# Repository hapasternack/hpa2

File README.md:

Copyright (c) 2020-2025 Henry A. Pasternack.  All rights reserved.

28-Jan-2026:
The project is up-to-date with KiCad 9.06. There are no ERC or DRC errors.

The project-local footprint library, HPA2-footprints.pretty, contains the following footprints.

   Custom footprints:
   1-pad-wire-connector-22-ga
   2-pad-wire-connector-22-ga
   2-pad-wire-connector-small
   3-pad-wire-connector-22-ga
   HPA-Output-Coil
   Semitec-CRD-SMD

   Legacy footprints to avoid breaking changes to the layout:
   TO-71-6
   D_DO-34_SOD68_P7.62mm_Horizontal
   D_DO-35_SOD27_P7.62mm_Horizontal
   R_0805_2012Metric_Pad1.15x1.40mm_HandSolder
   TO-126-3_Vertical
   TSOT-23-5

   All other footprints have been updated from the latest release libraries as of KiCad 9.0.6.

The project-local library, HPA2_symbols, contains the following custom schematic symbols.

   2N5564
   CRD
   ADA4627-1

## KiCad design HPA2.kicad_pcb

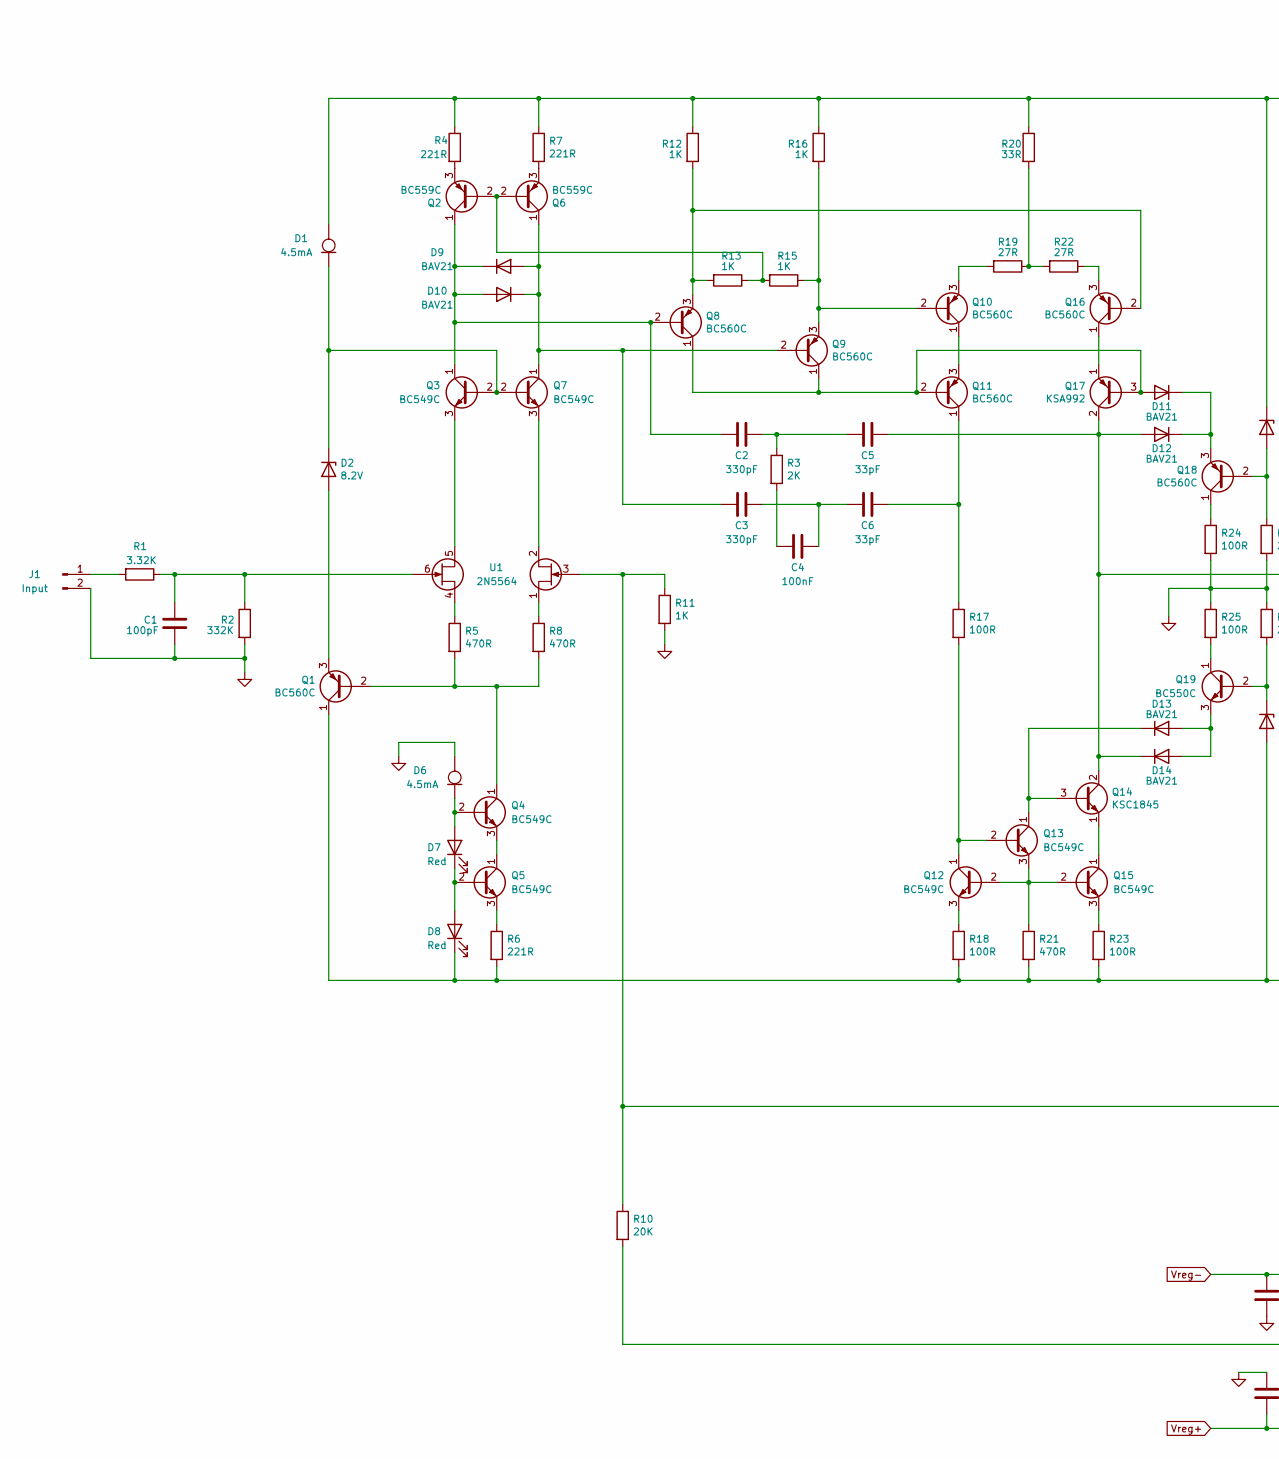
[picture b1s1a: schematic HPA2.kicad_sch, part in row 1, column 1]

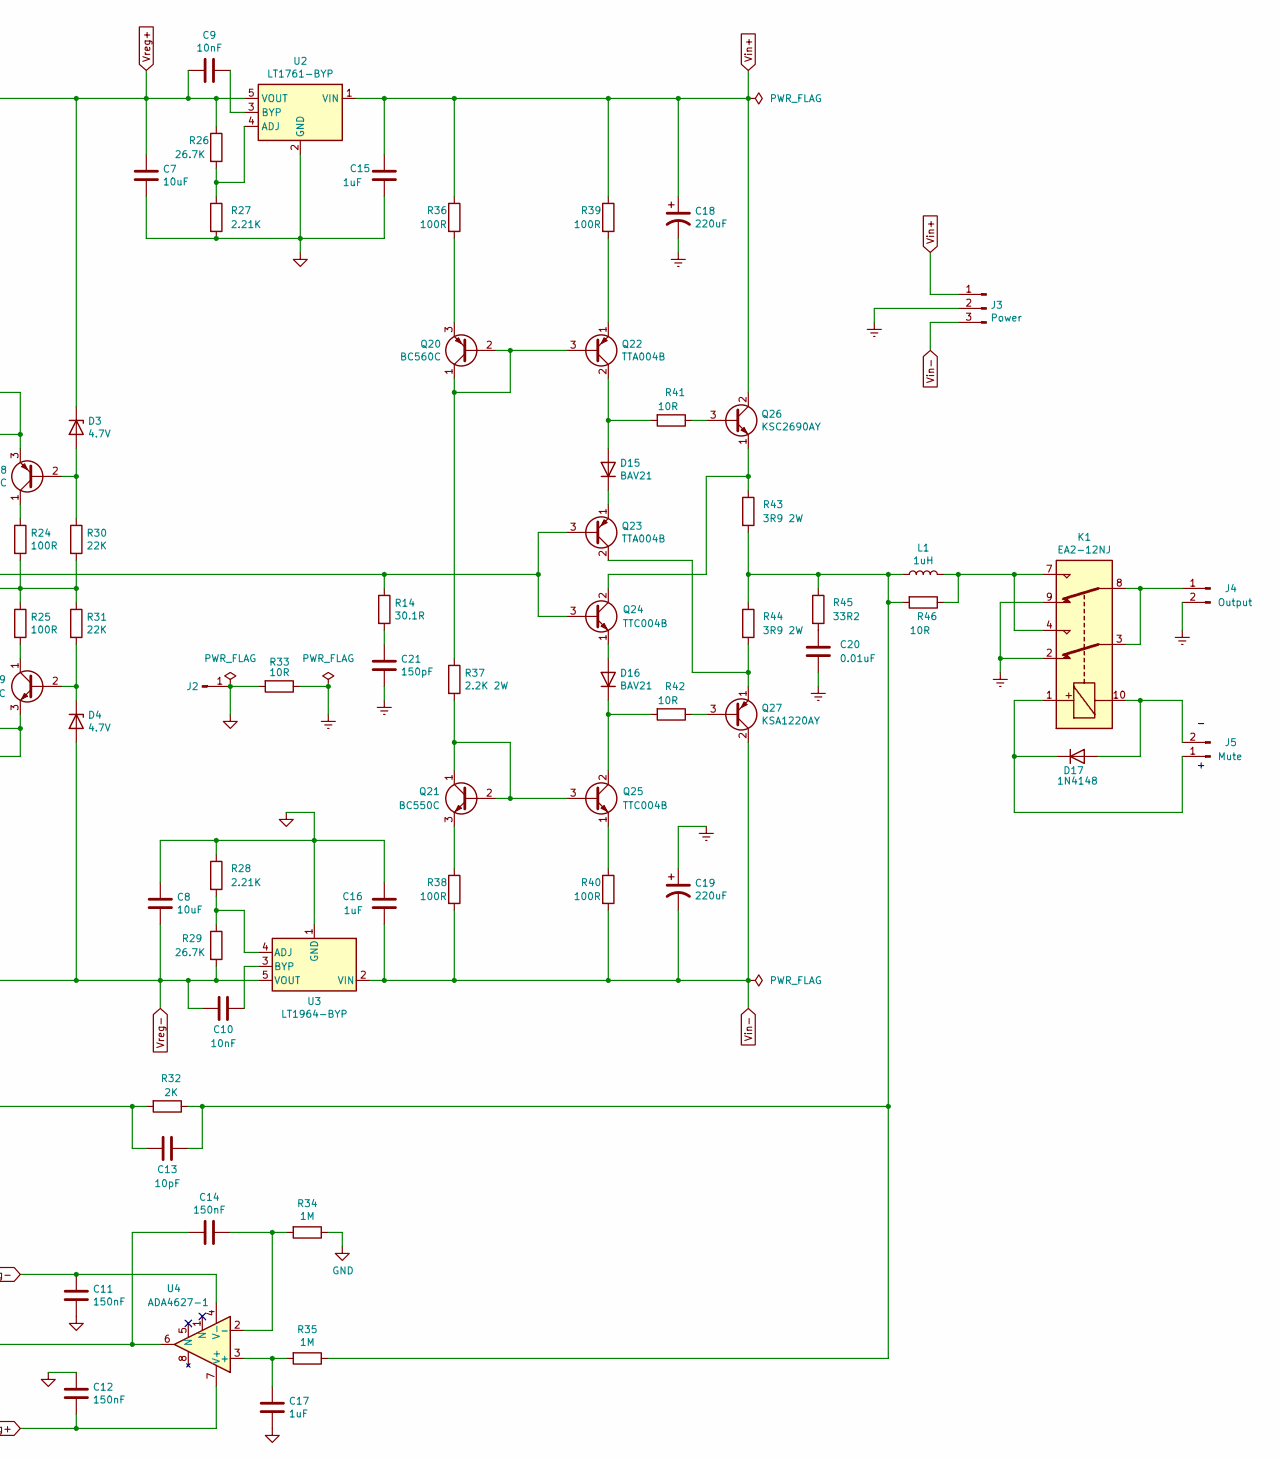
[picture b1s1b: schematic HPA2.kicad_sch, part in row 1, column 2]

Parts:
C1: 100pF; C_Disc_D3.8mm_W2.6mm_P2.50mm
C2, C3: 330pF; C_Disc_D3.8mm_W2.6mm_P2.50mm
C4: 100nF; C_Disc_D3.8mm_W2.6mm_P2.50mm
C5, C6: 33pF; C_Disc_D3.8mm_W2.6mm_P2.50mm
C7, C8: 10uF; C_1206_3216Metric_Pad1.33x1.80mm_HandSolder
C9, C10: 10nF; C_0805_2012Metric_Pad1.18x1.45mm_HandSolder
C11, C12, C14: 150nF; C_Rect_L7.2mm_W2.5mm_P5.00mm_FKS2_FKP2_MKS2_MKP2
C13: 10pF; C_Disc_D3.8mm_W2.6mm_P2.50mm
C15, C16: 1uF; C_1206_3216Metric_Pad1.33x1.80mm_HandSolder
C17: 1uF; C_Rect_L7.2mm_W5.5mm_P5.00mm_FKS2_FKP2_MKS2_MKP2
C18, C19: 220uF; CP_Radial_D10.0mm_P5.00mm
C20: 0.01uF; C_Disc_D4.7mm_W2.5mm_P5.00mm
C21: 150pF; C_Disc_D4.7mm_W2.5mm_P5.00mm
D1, D6: 4.5mA; Semitec-CRD-SMD
D2: 8.2V; D_DO-34_SOD68_P7.62mm_Horizontal
D3, D4: 4.7V; D_DO-34_SOD68_P7.62mm_Horizontal
D7, D8: Red; LED_D3.0mm
D9, D10, D11, D12, D13, D14, D15, D16: BAV21; D_DO-35_SOD27_P7.62mm_Horizontal
D17: 1N4148; D_DO-35_SOD27_P7.62mm_Horizontal
J1: Input; 2-pad-wire-connector-small
J2: Conn_01x01_Male; 1-pad-wire-connector-22-ga
J3: Power; 3-pad-wire-connector-22-ga
J4: Output; 2-pad-wire-connector-small
J5: Mute; 2-pad-wire-connector-22-ga
K1: EA2-12NJ; Relay_DPDT_Omron_G6H-2
L1: 1uH; HPA-Output-Coil
Q1, Q8, Q9, Q10, Q11, Q16, Q18, Q20: BC560C; TO-92_Inline
Q2, Q6: BC559C; TO-92_Inline
Q3, Q4, Q5, Q7, Q12, Q13, Q15: BC549C; TO-92_Inline
Q14: KSC1845; TO-92_Inline
Q17: KSA992; TO-92_Inline
Q19, Q21: BC550C; TO-92_Inline
Q22, Q23: TTA004B; TO-126-3_Vertical
Q24, Q25: TTC004B; TO-126-3_Vertical
Q26: KSC2690AY; TO-126-3_Vertical
Q27: KSA1220AY; TO-126-3_Vertical
R1: 3.32K; R_Axial_DIN0204_L3.6mm_D1.6mm_P5.08mm_Horizontal
R2: 332K; R_Axial_DIN0204_L3.6mm_D1.6mm_P5.08mm_Horizontal
R3: 2K; R_1206_3216Metric
R4, R6, R7: 221R; R_Axial_DIN0204_L3.6mm_D1.6mm_P5.08mm_Horizontal
R5, R8, R21: 470R; R_Axial_DIN0204_L3.6mm_D1.6mm_P5.08mm_Horizontal
R10: 20K; R_Axial_DIN0204_L3.6mm_D1.6mm_P5.08mm_Horizontal
R11, R12, R13, R15, R16: 1K; R_Axial_DIN0204_L3.6mm_D1.6mm_P5.08mm_Horizontal
R14: 30.1R; R_Axial_DIN0204_L3.6mm_D1.6mm_P5.08mm_Horizontal
R17, R18, R23, R24, R25, R36, R38, R39, R40: 100R; R_Axial_DIN0204_L3.6mm_D1.6mm_P5.08mm_Horizontal
R19, R22: 27R; R_Axial_DIN0204_L3.6mm_D1.6mm_P5.08mm_Horizontal
R20: 33R; R_Axial_DIN0204_L3.6mm_D1.6mm_P5.08mm_Horizontal
R26, R29: 26.7K; R_0805_2012Metric_Pad1.15x1.40mm_HandSolder
R27, R28: 2.21K; R_0805_2012Metric_Pad1.15x1.40mm_HandSolder
R30, R31: 22K; R_Axial_DIN0204_L3.6mm_D1.6mm_P5.08mm_Horizontal
R32: 2K; R_Axial_DIN0204_L3.6mm_D1.6mm_P5.08mm_Horizontal
R33, R41, R42, R46: 10R; R_Axial_DIN0207_L6.3mm_D2.5mm_P10.16mm_Horizontal
R34, R35: 1M; R_0805_2012Metric_Pad1.15x1.40mm_HandSolder
R37: 2.2K 2W; R_Axial_DIN0411_L9.9mm_D3.6mm_P12.70mm_Horizontal
R43, R44: 3R9 2W; R_Axial_DIN0411_L9.9mm_D3.6mm_P12.70mm_Horizontal
R45: 33R2; R_Axial_DIN0207_L6.3mm_D2.5mm_P10.16mm_Horizontal
U1: 2N5564; TO-71-6
U2: LT1761-BYP; TSOT-23-5
U3: LT1964-BYP; TSOT-23-5
U4: ADA4627-1; SOIC-8_3.9x4.9mm_P1.27mm

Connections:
GND: C1.2, C7.2, C8.1, C11.2, C12.1, C15.2, C16.2, C17.2, D6.2 (A), J1.2, J2.1, R2.2, R11.2, R24.2, R25.1, R27.2, R28.1, R30.2, R31.1, R33.2, R34.1, U2.2 (GND), U3.1 (GND)
GNDREF: C18.2, C19.1, C20.2, C21.2, J3.2, J4.2, K1.2, K1.9, R33.1
unnamed: C2.1, C5.2, R3.1
unnamed: C3.1, C4.1, C6.2
unnamed: C4.2, R3.2
unnamed: C13.1, L1.2, R32.1, R35.1, R43.2, R44.1, R45.1, R46.2
unnamed: C14.2, R10.2, U4.6
unnamed: C20.1, R45.2
unnamed: C21.1, R14.2
unnamed: D1.1 (K), D2.1 (K), Q3.2 (B), Q7.2 (B)
unnamed: D2.2 (A), Q1.3 (E)
unnamed: D3.2 (A), Q18.2 (B), R30.1
unnamed: D4.1 (K), Q19.2 (B), R31.2
unnamed: D6.1 (K), D7.2 (A), Q4.2 (B)
unnamed: D7.1 (K), D8.2 (A), Q5.2 (B)
unnamed: C2.2, D9.1 (K), D10.2 (A), Q2.1 (C), Q3.1 (C), Q8.2 (B)
unnamed: C3.2, D9.2 (A), D10.1 (K), Q6.1 (C), Q7.1 (C), Q9.2 (B)
unnamed: D11.2 (A), Q8.1 (C), Q9.1 (C), Q11.2 (B), Q17.3 (B)
unnamed: D11.1 (K), D12.1 (K), Q18.3 (E)
unnamed: C5.1, D12.2 (A), D14.1 (K), Q14.2 (C), Q17.2 (C), Q23.3 (B), Q24.3 (B), R14.1
unnamed: D13.2 (A), D14.2 (A), Q19.3 (E)
unnamed: D13.1 (K), Q13.1 (C), Q14.3 (B)
unnamed: D15.2 (A), Q22.2 (C), R41.2
unnamed: D15.1 (K), Q23.1 (E)
unnamed: D16.2 (A), Q24.1 (E)
unnamed: D16.1 (K), Q25.2 (C), R42.2
unnamed: D17.2 (A), J5.2, K1.10
unnamed: D17.1 (K), J5.1, K1.1
unnamed: J1.1, R1.2
unnamed: J4.1, K1.3, K1.8
unnamed: K1.4, K1.7, L1.1, R46.1
unnamed: Q1.2 (B), Q4.1 (C), R5.2, R8.2
unnamed: Q2.2 (B), Q6.2 (B), R13.1, R15.2
unnamed: Q2.3 (E), R4.2
unnamed: Q3.3 (E), U1.5 (2D)
unnamed: Q4.3 (E), Q5.1 (C)
unnamed: Q5.3 (E), R6.1
unnamed: Q6.3 (E), R7.2
unnamed: Q7.3 (E), U1.2 (1D)
unnamed: Q9.3 (E), Q10.2 (B), R15.1, R16.2
unnamed: Q10.1 (C), Q11.3 (E)
unnamed: Q10.3 (E), R19.2
unnamed: C6.1, Q11.1 (C), R17.1
unnamed: Q12.2 (B), Q13.3 (E), Q15.2 (B), R21.1
unnamed: Q12.1 (C), Q13.2 (B), R17.2
unnamed: Q12.3 (E), R18.1
unnamed: Q14.1 (E), Q15.1 (C)
unnamed: Q15.3 (E), R23.1
unnamed: Q8.3 (E), Q16.2 (B), R12.2, R13.2
unnamed: Q16.1 (C), Q17.1 (E)
unnamed: Q16.3 (E), R22.1
unnamed: Q18.1 (C), R24.1
unnamed: Q19.1 (C), R25.2
unnamed: Q20.1 (C), Q20.2 (B), Q22.3 (B), R37.1
unnamed: Q20.3 (E), R36.2
unnamed: Q21.1 (C), Q21.2 (B), Q25.3 (B), R37.2
unnamed: Q21.3 (E), R38.1
unnamed: Q22.1 (E), R39.2
unnamed: Q23.2 (C), Q27.1 (E), R44.2
unnamed: Q24.2 (C), Q26.1 (E), R43.1
unnamed: Q25.1 (E), R40.1
unnamed: Q26.3 (B), R41.1
unnamed: Q27.3 (B), R42.1
unnamed: R19.1, R20.2, R22.2
unnamed: C13.2, R10.1, R11.1, R32.2, U1.3 (1G)
unnamed: R8.1, U1.1 (1S)
unnamed: C1.1, R1.1, R2.1, U1.6 (2G)
unnamed: R5.1, U1.4 (2S)
unnamed: R26.2, R27.1, U2.4 (ADJ)
unnamed: C9.1, U2.3 (BYP)
unnamed: R28.2, R29.1, U3.4 (ADJ)
unnamed: C10.1, U3.3 (BYP)
unnamed: C17.1, R35.2, U4.3 (+)
unnamed: C14.1, R34.2, U4.2 (-)
Vin+: C15.1, C18.1, J3.1, Q26.2 (C), R36.1, R39.1, U2.1 (VIN)
Vin-: C16.1, C19.2, J3.3, Q27.2 (C), R38.2, R40.2, U3.2 (VIN)
Vreg+: C7.1, C9.2, C12.2, D1.2 (A), D3.1 (K), R4.1, R7.1, R12.1, R16.1, R20.1, R26.1, U2.5 (VOUT), U4.7 (V+)
Vreg-: C8.2, C10.2, C11.1, D4.2 (A), D8.1 (K), Q1.1 (C), R6.2, R18.2, R21.2, R23.2, R29.2, U3.5 (VOUT), U4.4 (V-)

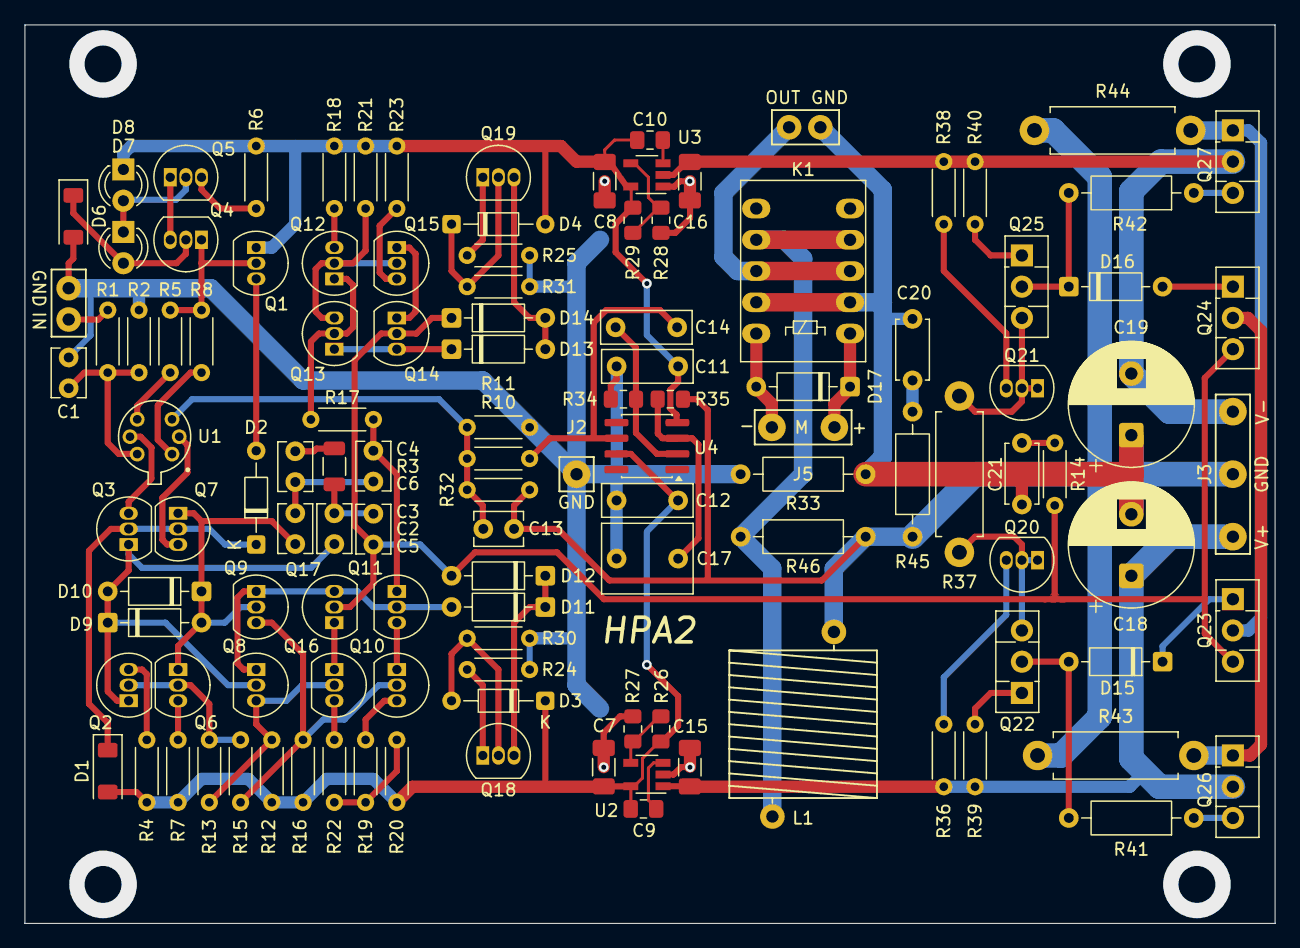
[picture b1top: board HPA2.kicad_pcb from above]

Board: 2 copper layers, 101.6 x 73.0 mm, 120 parts (0 on the bottom side), 78 nets.

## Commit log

2025-12-11 Removing legacy files from project.
2026-01-21 On the schematic: - Aligned schematic to grid. - Changed all default library transistor symbols to generic Q_PNP/Q_NPN symbols. - Updated other out-of-date default library symbols - Added GND_PWR fla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
2026-01-28 - Created project-local symbol library - Copied custom 2N5564, CRD, and ADA4627-1 symbols to the library - Deleted HPA2-rescue library
2026-01-28 - Removed useless triangular copper pours at trace butt joints - Separated footprints of thermally connected transistor pairs to fix DRC warnings
2026-01-28 Loaded the existing TSOT-23-5 footprint from the board and saved it to the project-local footprint library. Updated the board. This prevents breaking the U2 regulator layout when updating from latest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
2026-01-28 Copied the HPA-Output-Coil footprint to the project-local library and updated the board.
2026-01-28 Updated DO-34 footprint to move "K" silkscreen to f-fab, and made sure the footprint is in the porject-local library. Updated board.
2026-01-28 -Added local symbol and footprint libraries to repo -Fixed HPA-Output-Coil courtyard
2026-01-28 Copied TO-126-3-Vertical footprint into project-local library and updated board.
2026-01-28 Updated remaining footprints from library except for Resistor_SMD:R_0805_2012Metric_Pad1.15x1.40mm_HandSolder.
2026-01-28 Vendored Resistor_SMD:R_0805_2012Metric_Pad1.15x1.40mm_HandSolder. Updated board.
2026-01-28 Added legacy R_0805_2012Metric_Pad1.15x1.40mm_HandSolder footprint to project-local library.
2026-01-28 Updated schematic to be consistent with PCB footprint changes.
2026-01-29 Added custom wire-to-board footprints. Updated the README.
2026-01-29 Updated AD4627-1 symbol to have unconnected pin 8.
2026-01-29 Updated symbols and footprints following KiCad update to 9.0.7.
